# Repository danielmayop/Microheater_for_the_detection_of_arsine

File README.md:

# Microcalentador para la detección de arsina

Microcalentador con control de temperatura para un sensor de arsina. El repositorio reúne el firmware y los scripts, el diseño de la placa, las simulaciones y las mediciones.

| Carpeta | Contenido |
|---|---|
| `Codigos/` | Firmware del controlador y scripts de MATLAB para identificar el modelo |
| `Kicad/` | Esquemático y placa del controlador de temperatura |
| `LTspice/` | Simulaciones |
| `Imagenes/`, `Hoja de datos/`, `paper/` | Fotos, gráficas y documentación |

## Respuesta transitoria del microcalentador (encendido y apagado)

Se midió la temperatura del microcalentador con duty de 30, 40, 50, 60, 70, 80, 90 y 100 %: unos 10 min encendido y luego el enfriamiento, en dos configuraciones:

- **Aire libre:** sensor sobre la parte resistiva.
- **Dentro de la caja:** el microcalentador dentro de una caja, midiendo la temperatura de su interior.

**Parte resistiva, aire libre**

**Dentro de la caja**

### Conclusiones del transitorio

**Encendido.** Las curvas suben a velocidades distintas porque cada duty apunta a una temperatura final distinta: cuanto mayor es el duty, más alta es la temperatura que se busca alcanzar y más rápido sube al principio. Sin embargo, el tiempo que tarda el microcalentador en responder es esencialmente el mismo sin importar el duty: todas las curvas tienen la misma forma y lo único que cambia es su escala. Por eso, al aire libre, el calentamiento se describe bien como un sistema de primer orden con una única constante de tiempo, y el aumento final de temperatura crece de forma proporcional al duty. Dentro de la caja el sensor ve un calentamiento menor y bastante más lento, y la respuesta ya no tiene un solo tiempo característico: hay una parte rápida, parecida a la del calentador al aire libre, y otra mucho más lenta que sigue evolucionando cuando se apaga el calentador, de modo que nunca llega a un régimen estacionario durante la medición.

**Apagado.** Al apagar, lo más caliente se enfría más rápido en valores absolutos, pero eso también le pasa a cualquier sistema lineal, así que por sí solo no demuestra no linealidad. Lo que sí la muestra es comparar las curvas normalizadas: al aire libre, cuanto más caliente está el microcalentador, más rápido se enfría en proporción, algo esperable si las pérdidas de calor hacia el ambiente crecen con la temperatura. Dentro de la caja no se ve esa dependencia, y el enfriamiento tiene una cola lenta: pasados varios minutos desde el apagado la temperatura todavía no volvió a la inicial, por lo que el registro es corto para fijar bien su constante de tiempo de enfriamiento.

### Función de transferencia

Cada curva se ajustó con un modelo de primer orden (`Codigos/Matlab Modelo/construir_tf.m`):

- Encendido: `G_on(s) = K_on / (τ_on·s + 1)`, con `K_on` en °C (el aumento final de temperatura para ese duty) y `τ_on` en s.
- Apagado: `G_off(s) = 1 / (τ_off·s + 1)`, con `τ_off` en s.

**Parte resistiva, aire libre**

| Duty [%] | K_on [°C] | τ_on [s] | τ_off [s] | T_amb [°C] | G_on(s) |
|---:|---:|---:|---:|---:|---|
| 100 | 36,693 | 81,355 | 56,548 | 23,658 | `36,693 / (81,355·s + 1)` |
| 90 | 35,373 | 65,085 | 66,869 | 23,483 | `35,373 / (65,085·s + 1)` |
| 80 | 32,303 | 72,815 | 63,468 | 23,336 | `32,303 / (72,815·s + 1)` |
| 70 | 27,813 | 71,551 | 65,861 | 23,248 | `27,813 / (71,551·s + 1)` |
| 60 | 23,95 | 74,366 | 70,117 | 22,567 | `23,95 / (74,366·s + 1)` |
| 50 | 19,382 | 61,978 | 68,129 | 22,578 | `19,382 / (61,978·s + 1)` |
| 40 | 15,919 | 73,312 | 66,356 | 22,53 | `15,919 / (73,312·s + 1)` |
| 30 | 11,922 | 67,811 | 72,854 | 22,109 | `11,922 / (67,811·s + 1)` |

**Dentro de la caja**

| Duty [%] | K_on [°C] | τ_on [s] | τ_off [s] | T_amb [°C] | G_on(s) |
|---:|---:|---:|---:|---:|---|
| 100 | 26,89 | 116,03 | 130,21 | 24,323 | `26,89 / (116,03·s + 1)` |
| 90 | 23,252 | 115,96 | 125,4 | 24,625 | `23,252 / (115,96·s + 1)` |
| 80 | 20,22 | 120,34 | 148,24 | 24,032 | `20,22 / (120,34·s + 1)` |
| 70 | 18,15 | 119,87 | 125,55 | 24,134 | `18,15 / (119,87·s + 1)` |
| 60 | 15,551 | 138,71 | 131,22 | 23,7 | `15,551 / (138,71·s + 1)` |
| 50 | 12,525 | 117,3 | 154,28 | 23,328 | `12,525 / (117,3·s + 1)` |
| 40 | 9,8572 | 124,09 | 126,49 | 23,1 | `9,8572 / (124,09·s + 1)` |
| 30 | 7,6401 | 116,94 | 140,92 | 22,901 | `7,6401 / (116,94·s + 1)` |

Son los valores que entrega `main_comparacion_duty.m`. En la caja el modelo de primer orden es una aproximación: la curva tiene dos escalas de tiempo, y los `t_on`/`t_off` que usa el script no coinciden con los datos en varias corridas.

## Etapa de amplificación de corriente

El ESP32 genera la señal PWM (en el firmware: GPIO 25, 1 kHz, 8 bits de resolución), pero no puede entregar la corriente que necesita el microcalentador. Por eso la señal pasa por tres etapas en cascada: un **optoacoplador**, un **transistor bipolar (BJT)** y un **MOSFET** que conmuta la corriente del calentador.

La fuente `V1` representa la salida PWM del ESP32 (pulso de 0 a 3 V, período de 1 ms, 0,5 ms en alto, es decir 50 % de duty) y `V2` es la alimentación `Vcc` de 5,5 V.

### Etapas del circuito

1. **Optoacoplador (`U1`, `R1`, `R2`).** La señal del ESP32 enciende el LED del optoacoplador a través de `R1` (330 Ω), que fija la corriente del LED. El fototransistor de salida conduce cuando el LED está encendido y `R2` (4,6 kΩ) a masa mantiene su salida en 0 V cuando el LED está apagado. La función de esta etapa es acoplar la lógica del ESP32 con la etapa de potencia sin conectarlas eléctricamente.
2. **BJT como seguidor por emisor (`Q1`, `R4`, `R5`).** La salida del optoacoplador es una señal débil: puede entregar muy poca corriente. El transistor `Q1` funciona como un "refuerzo" de esa señal, sin cambiarla.
   - **Qué hace.** El optoacoplador maneja solo una corriente muy pequeña (la de la base de `Q1`), y `Q1` entrega por el emisor una corriente mucho mayor, tomada de `Vcc`, para cargar la compuerta del MOSFET.
   - **Qué tensión entrega.** La tensión del emisor copia a la de la base, unos 0,7 V más baja. Por eso se llama "seguidor": la salida sigue a la entrada. Si el optoacoplador pone la base en alto, el emisor queda en alto; si la pone en 0 V, el emisor baja a 0 V.
   - **`R5` (330 Ω).** Está entre el emisor y la compuerta del MOSFET y limita el pico de corriente al cargar la compuerta.
   - **`R4` (10 kΩ).** Va de la compuerta a masa y la descarga cuando `Q1` deja de conducir, porque el seguidor solo puede entregar corriente, no absorberla. Sin `R4`, la compuerta quedaría cargada y el MOSFET no se apagaría.
3. **MOSFET como interruptor (`M1`, `R6`, `R3`).** `M1` (IRFHM830) tiene la fuente a masa y se comporta como un interruptor: con la compuerta alta conduce y con la compuerta en 0 V se corta. La corriente la fijan `Vcc` y las resistencias en serie: `R3` (0,75 Ω) representa al microcalentador y `R6` (4,8 Ω) es la resistencia serie.

### Resultado de la simulación

La traza verde es la tensión sobre `R3` (el calentador) y la azul la corriente que lo atraviesa, durante 10 ms (10 períodos). Son pulsos cuadrados con el mismo período y el mismo ancho que la señal de entrada: la corriente es cero con el PWM en bajo y se mantiene constante, en un valor cercano a 1 A, con el PWM en alto. Es decir, las tres etapas transmiten el PWM sin deformarlo de forma apreciable a esta escala.

### Simulación y placa

La simulación usa componentes distintos de los de la placa (`Kicad/Controlador_temp/`), con la misma topología:

| Función | Simulación (LTspice) | Placa (KiCad) |
|---|---|---|
| Entrada | `V1`, pulso de 0 a 3 V, 1 kHz | PWM del ESP32 (GPIO 25) |
| Optoacoplador | `U1`, 4N25 | `U2`, 4N35 |
| Resistencia del LED | `R1`, 330 Ω | `R3`, 330 Ω |
| Resistencia a masa del fototransistor | `R2`, 4,6 kΩ | `preset2`, trimmer de 5 kΩ |
| BJT | `Q1`, 2N3904 | `Q1`, BD911 |
| Resistencia a masa del emisor | `R4`, 10 kΩ | `R5`, 10 kΩ |
| Resistencia de compuerta | `R5`, 330 Ω | `R6`, 330 Ω |
| MOSFET | `M1`, IRFHM830 | `Q2`, IRLZ44N |
| Resistencia serie | `R6`, 4,8 Ω | `Rs1`, 4,8 Ω |
| Microcalentador | `R3`, 0,75 Ω | conector `Calent1` |
| Alimentación | `V2`, 5,5 V | módulo `PS1` (MC00100) |

## Controlador: on-off frente a PID

Para mantener el microcalentador en la temperatura de consigna (*setpoint*) se compararon dos estrategias de control habituales: el controlador **on-off** (con histéresis) y el controlador **PID**. En este proyecto se eligió el **on-off**.

### Descripción breve

**On-off (todo o nada).** La salida solo tiene dos estados: encendida o apagada. En calefacción se enciende por debajo del setpoint y se apaga por encima, por lo que la temperatura oscila de forma continua alrededor de la consigna. Para evitar conmutaciones muy rápidas se agrega una **histéresis** (una banda alrededor del setpoint): una banda más ancha reduce la frecuencia de conmutación pero aumenta la oscilación y el sobreimpulso. Es el esquema más simple y barato, y se usa donde no se necesita gran precisión ([x-engineer](https://x-engineer.org/?p=3309), [Omega](https://es.omega.com/temperature/Z/controlleroperation.html)).

**PID.** Calcula una salida continua combinando tres acciones sobre el error: la proporcional (reacciona al error actual), la integral (elimina el error permanente acumulándolo) y la derivativa (anticipa la tendencia). Es más preciso y estable que el on-off, pero exige **sintonizar** tres parámetros y es más complejo ([Omega](https://es.omega.com/temperature/Z/controlleroperation.html)). En sistemas térmicos lentos o con retardo, la acción integral puede acumularse mientras la salida está saturada (*integral windup*) y provocar sobreimpulso y oscilaciones, por lo que requiere medidas anti-windup y una sintonización conservadora ([Industrial Monitor Direct](https://industrialmonitordirect.com/blogs/knowledgebase/pid-integral-windup-fix-for-slow-temperature-control-systems)).

### Comparación

| Aspecto | On-off con histéresis | PID |
|---|---|---|
| Salida | Solo encendido o apagado | Continua (duty variable) |
| Precisión en el setpoint | Oscila dentro de una banda | Alta, sin error permanente (con acción integral) |
| Sobreimpulso | Presente, crece con la histéresis | Puede minimizarse si está bien sintonizado |
| Complejidad | Muy baja (una comparación) | Mayor: tres parámetros y anti-windup |
| Sintonización | Solo el ancho de la histéresis | Requiere un modelo o ensayos |
| Conmutación | Frecuente | Salida más suave |
| Recursos | Mínimos | Cálculo periódico con tiempo de muestreo fijo |

### Ventajas y desventajas para este microcalentador

**Ventajas del on-off en esta aplicación**

- **Implementación mínima.** En el firmware (`control.cpp`) el control es una comparación con histéresis de 1 °C: se enciende por debajo de `setpoint - 1 °C`, se apaga al llegar al `setpoint` y mantiene su estado dentro de la banda. No necesita tiempo de muestreo fijo ni parámetros que sintonizar.
- **Sin desgaste por conmutación.** La conmutación se hace con un MOSFET (etapa de amplificación de corriente) y no con un relé mecánico, así que la conmutación frecuente no es un problema de vida útil, que es la principal desventaja habitual del on-off.
- **Dinámica lenta y relativamente simple.** El microcalentador responde como un sistema de primer orden con constante de tiempo de ≈ 1 min al aire libre, por lo que una banda de 1 °C da ciclos de conmutación de varios segundos o más y no a una frecuencia que el MOSFET no pueda seguir.
- **Calentamiento más rápido.** Al encender con el 100 % de duty el sistema sube con la máxima velocidad que permite la etapa de potencia, sin esperar a que un integrador acumule.
- **Seguridad sencilla.** Junto con el límite de 80 °C del firmware y el apagado ante lectura inválida del NTC, el comportamiento es fácil de verificar.

**Desventajas del on-off en esta aplicación**

- **Rizado de temperatura.** La temperatura nunca queda fija: oscila alrededor del setpoint con una amplitud que depende de la histéresis y de la inercia térmica. Si la detección de arsina fuera sensible a pequeñas variaciones de la temperatura del sensor, esto sería la limitación principal.
- **Sobreimpulso por el retardo.** El NTC no está exactamente sobre la resistencia calefactora, y en la caja el sistema tiene dos escalas de tiempo (≈ 1 min y ≈ 5–9 min). Al apagar, la temperatura puede seguir subiendo un poco antes de bajar, y el calor remanente ocasiona que el exceso sobre la consigna dependa de las condiciones de la medición.
- **Potencia máxima en cada ciclo.** Siempre se calienta con la potencia total (≈ 4,7 W disipados en `R6` según la simulación), lo que genera más estrés térmico y un consumo pico mayor que un control que reduce la potencia al acercarse al setpoint.
- **No aprovecha el PWM.** La etapa de potencia ya permite variar el duty (PWM de 1 kHz y 8 bits en el GPIO 25), pero en el esquema on-off solo se usan los valores 0 y 255.

**Qué aportaría un PID**

- Una salida suave: al acercarse a la temperatura deseada reduciría el duty y el rizado sería mucho menor, con error permanente nulo.
- Un mejor desempeño ante perturbaciones como cambios de temperatura ambiente, caja o corrientes de aire, que modifican las pérdidas térmicas.
- Como costo, habría que sintonizarlo y proteger la acción integral contra *windup* durante el calentamiento inicial, donde el actuador está saturado al 100 %.

### Elección para el proyecto

Se eligió el **controlador on-off con histéresis** porque la aplicación no exige regulación de alta precisión, la implementación es muy simple y robusta en el ESP32 y la conmutación del MOSFET no sufre desgaste. A cambio se acepta un rizado de temperatura acotado por la histéresis de 1 °C.

Si más adelante se necesitara menor rizado, los modelos identificados en la sección de la función de transferencia (ganancia estática ≈ 0,40 °C por % de duty y constante de tiempo ≈ 60 s al aire libre) y el PWM ya disponible en el hardware permitirían sintonizar un PID sin modificar la placa.

### Fuentes

- [On-off control system (x-engineer.org)](https://x-engineer.org/?p=3309)
- [Controladores on-off, proporcionales y PID (Omega)](https://es.omega.com/temperature/Z/controlleroperation.html)
- [PID integral windup en sistemas lentos de temperatura (Industrial Monitor Direct)](https://industrialmonitordirect.com/blogs/knowledgebase/pid-integral-windup-fix-for-slow-temperature-control-systems)

## Análisis de la ESP32 DevKit V1

La placa de desarrollo ESP32 DevKit V1 ejecuta el control de temperatura, lee los sensores, maneja la pantalla, genera el PWM de la etapa de potencia y transmite los datos por Bluetooth.

### Tabla de entradas y salidas

Se listan los pines que se usan en la placa (según el esquemático) y en el firmware (`Codigos/Arduino IDE ESP32/control_temperatura ver 2/ControlTemperatura/`). Los pines marcados como "previsto" están conectados a un conector de la placa, pero el firmware actual no los usa.

| GPIO | Nombre en la placa | Función en el proyecto | Tipo | Entrada / salida |
|---|---|---|---|---|
| 2 | `D2` | LED de estado: encendido con el sistema activo, apagado con el sistema apagado o ante una falla (NTC inválido o sobretemperatura) | Digital | Salida |
| 5 | `D5` | Datos del segundo sensor DHT22 (previsto) | Digital | Entrada / salida |
| 12 | `D12` | `SO` del módulo MAX6675 (opcional, previsto) | Digital (SPI) | Entrada |
| 13 | `D13` | `CS` del módulo MAX6675 (opcional, previsto) | Digital (SPI) | Salida |
| 14 | `D14` | `SCK` del módulo MAX6675 (opcional, previsto) | Digital (SPI) | Salida |
| 16 | `RX2` | `SDA` del bus I2C (400 kHz) hacia la pantalla OLED SSD1306 (dirección `0x3C`) | Digital (I2C) | Entrada / salida |
| 17 | `TX2` | `SCL` del bus I2C hacia la pantalla OLED | Digital (I2C) | Salida |
| 18 | `D18` | Datos del sensor DHT22 (temperatura ambiente y humedad, cada 2 s) | Digital | Entrada / salida |
| 25 | `D25` | Señal PWM (1 kHz, 8 bits) hacia el optoacoplador de la etapa de potencia; con el control on-off toma solo los valores 0 y 255 | PWM | Salida |
| 26 | `D26` | Interruptor de encendido del sistema (pull-up interno; ON = conectado a GND) | Digital | Entrada |
| 34 | `D34` | Potenciómetro que fija el setpoint (ADC de 12 bits) | Analógico (ADC1) | Entrada |
| 35 | `D35` | Divisor del termistor NTC de 10 kΩ, temperatura real usada por el control (ADC de 12 bits, 0 a 3,3 V) | Analógico (ADC1) | Entrada |
| — | `3V3` | Alimentación de 3,3 V para el potenciómetro, el divisor del termistor, los pull-up, la pantalla, el MAX6675 y los DHT22 | Alimentación | Salida |
| — | `GND` | Masa común de la placa | Alimentación | — |
| — | `VIN` | Entrada de 5,5 V desde el módulo reductor (`Vcc`) a través del diodo `D1` | Alimentación | Entrada |

El monitor serie usa el UART0 (`TX0` y `RX0`, GPIO 1 y 3) a través del puerto USB, y el Bluetooth (BLE) es interno del módulo, por lo que no ocupan pines de la placa.

## Diseño PCB

La placa se diseñó en KiCad (`Kicad/Controlador_temp/`). El esquemático reúne en una sola placa la alimentación, la ESP32 DevKit V1, la etapa de potencia del microcalentador y los conectores de los sensores y de la pantalla.

### Etapas de la placa

- **Alimentación.** La placa se alimenta con 19 V a través de un conector *jack* (`J1`). El pulsador `Btn2` está en serie con la entrada y enciende y apaga la alimentación de toda la placa. Un módulo reductor DC-DC (`PS1`, MC00100) baja los 19 V a 5,5 V (red `Vcc`), con un capacitor de 1000 µF (`C2`) en la salida. Esa tensión alimenta la etapa de potencia y, a través de un diodo Schottky (`D1`), el pin `VIN` de la ESP32, que genera los 3,3 V (`3V3`) para los sensores y la pantalla.
- **Microcontrolador.** La ESP32 DevKit V1 (`U1`) ejecuta el control de temperatura. El pulsador `Btn1` (con `R1` de 330 Ω) está conectado al GPIO 26 (`boton1`) y enciende y apaga el sistema de control. Los pines que usa el firmware están en la sección anterior.
- **Etapa de amplificación de corriente.** Es la que se describió en la sección anterior: el PWM del GPIO 25 pasa por el optoacoplador 4N35 (`U2`), un BJT BD911 (`Q1`) y un MOSFET IRLZ44N (`Q2`), que conmuta la corriente del microcalentador conectado al terminal `Calent1` en serie con `Rs1` de 4,8 Ω.
- **Consigna de temperatura.** El potenciómetro `RV1`, alimentado con 3,3 V, entrega al GPIO 34 (`potenc`) la tensión que fija la temperatura a la que se quiere llevar el microcalentador.
- **Medición de temperatura.** El conector `J4` recibe el termistor, que junto con la resistencia `R2` de 100 kΩ forma un divisor de tensión cuya salida va al GPIO 35 (`D35`).
- **Pantalla.** El conector `J2` lleva `GND`, `3V3` y las líneas `SDA` y `SCL` del bus I2C hacia la pantalla LCD/OLED.
- **Termocupla (opcional).** El conector `J3` está previsto para un módulo MAX6675, conectado por SPI (`SCK`, `SO`, `CS`) a los GPIO 14, 12 y 13. Es opcional y el firmware actual no lo usa.
- **Sensores de temperatura y humedad.** Los conectores `J5` y el de `SENS-1` permiten conectar dos sensores DHT (en el esquemático figuran como DHT22; el DHT21 usa el mismo protocolo de un solo hilo), con resistencias de pull-up de 10 kΩ a 3,3 V (`R4` y `R7`) sobre las líneas `DHT22_1` (GPIO 18) y `DHT22_2` (GPIO 5). El firmware actual solo lee el primero.

### Lista de componentes

| Referencia | Componente | Valor / modelo | Cant. |
|---|---|---|---|
| `U1` | Placa de desarrollo | ESP32 DevKit V1 | 1 |
| `PS1` | Módulo reductor DC-DC | MC00100 (LM2596) | 1 |
| `U2` | Optoacoplador | 4N35 | 1 |
| `Q1` | Transistor BJT | BD911 | 1 |
| `Q2` | MOSFET canal N | IRLZ44N | 1 |
| `D1` | Diodo | Tipo Schottky (DO-41) | 1 |
| `C2` | Capacitor electrolítico | 1000 µF | 1 |
| `R1`, `R3`, `R6` | Resistencia | 330 Ω | 3 |
| `R4`, `R5`, `R7` | Resistencia | 10 kΩ | 3 |
| `R2` | Resistencia | 100 kΩ | 1 |
| `Rs1` | Resistencia de potencia | 4,8 Ω | 1 |
| `preset2` | Trimmer | 5 kΩ | 1 |
| `RV1` | Potenciómetro | Lineal | 1 |
| `J1` | Conector jack DC | 19 V | 1 |
| `Btn1`, `Btn2`, `Calent1` | Bornera de 2 pines | 5,08 mm | 3 |
| `J4` | Conector del termistor | 2 pines | 1 |
| `J2`, `J3`, `J5` | Conector JST XH | 5 pines | 3 |
| `SENS-1` | Sensor de temperatura y humedad | DHT22 | 1 |
| `H1` a `H4` | Perforación de montaje | M3 | 4 |

### Diseño y placa real

Arriba se ve el diseño 3D generado en KiCad y abajo la placa fabricada, por la cara superior (izquierda) y la cara inferior (derecha). Las fotos de la placa real están giradas 90° para compararlas con el diseño.

La placa real respeta el diseño: mantiene la distribución de las etapas, las pistas de las dos caras, las perforaciones de montaje y la serigrafía (nombres de conectores, referencias de componentes y la inscripción "PROYECTO 2026"). El módulo reductor figura serigrafiado como `STEP DOWN LM2596` y el módulo de la ESP32 tiene el recorte para su antena. Las fotos corresponden a la placa sin componentes soldados, con todas las perforaciones y pads listos para el montaje.

## Conexión a la página

Los datos que envía la ESP32 se visualizan en una página web, **GIAQA Monitoreo Bluetooth**, diseñada en Lovable. La ESP32 transmite por Bluetooth de baja energía (BLE) y la página se conecta directamente desde el navegador mediante Web Bluetooth.

**Enlace a la página:** [https://id-preview--22e80b2b-a717-4908-83b7-207b0a4aaa5b.lovable.app](https://id-preview--22e80b2b-a717-4908-83b7-207b0a4aaa5b.lovable.app)

**Proyecto en Lovable:** [BLE Dashboard](https://lovable.dev/projects/22e80b2b-a717-4908-83b7-207b0a4aaa5b)

### Qué hace la página

- **Mediciones.** Permite conectar la ESP32 por Bluetooth, recibir las variables en tiempo real (temperatura real, temperatura y humedad del DHT22, setpoint, estado del calentador y tiempo) y graficarlas en vivo. Incluye un registro de eventos de la conexión, el inicio y la pausa de la adquisición, y un modo de simulación para probar la página sin la placa.
- **Procesamiento.** Ofrece herramientas para procesar y analizar los datos adquiridos.
- **Historial y exportación.** Se pueden guardar las mediciones, revisarlas, graficarlas, renombrarlas, eliminarlas y exportarlas en formato CSV o TXT.
- **Cuentas y mediciones compartidas.** Hay perfiles de usuario opcionales y se pueden compartir mediciones en vivo, en modo solo lectura, mediante códigos de acceso.
- **Teoría y guías.** Tiene secciones de contenido teórico y guías de uso.

### Cómo se comunica con la ESP32

La ESP32 se publica como servidor BLE con el servicio *Nordic UART* (NUS). Envía los datos por notificaciones en la característica de transmisión, en mensajes con formato JSON (por ejemplo, `temperatura_real`, `setpoint`, `calentador`), y la página puede enviarle comandos por la característica de recepción. La conexión requiere un navegador con Web Bluetooth, como Chrome o Edge en escritorio o en Android.

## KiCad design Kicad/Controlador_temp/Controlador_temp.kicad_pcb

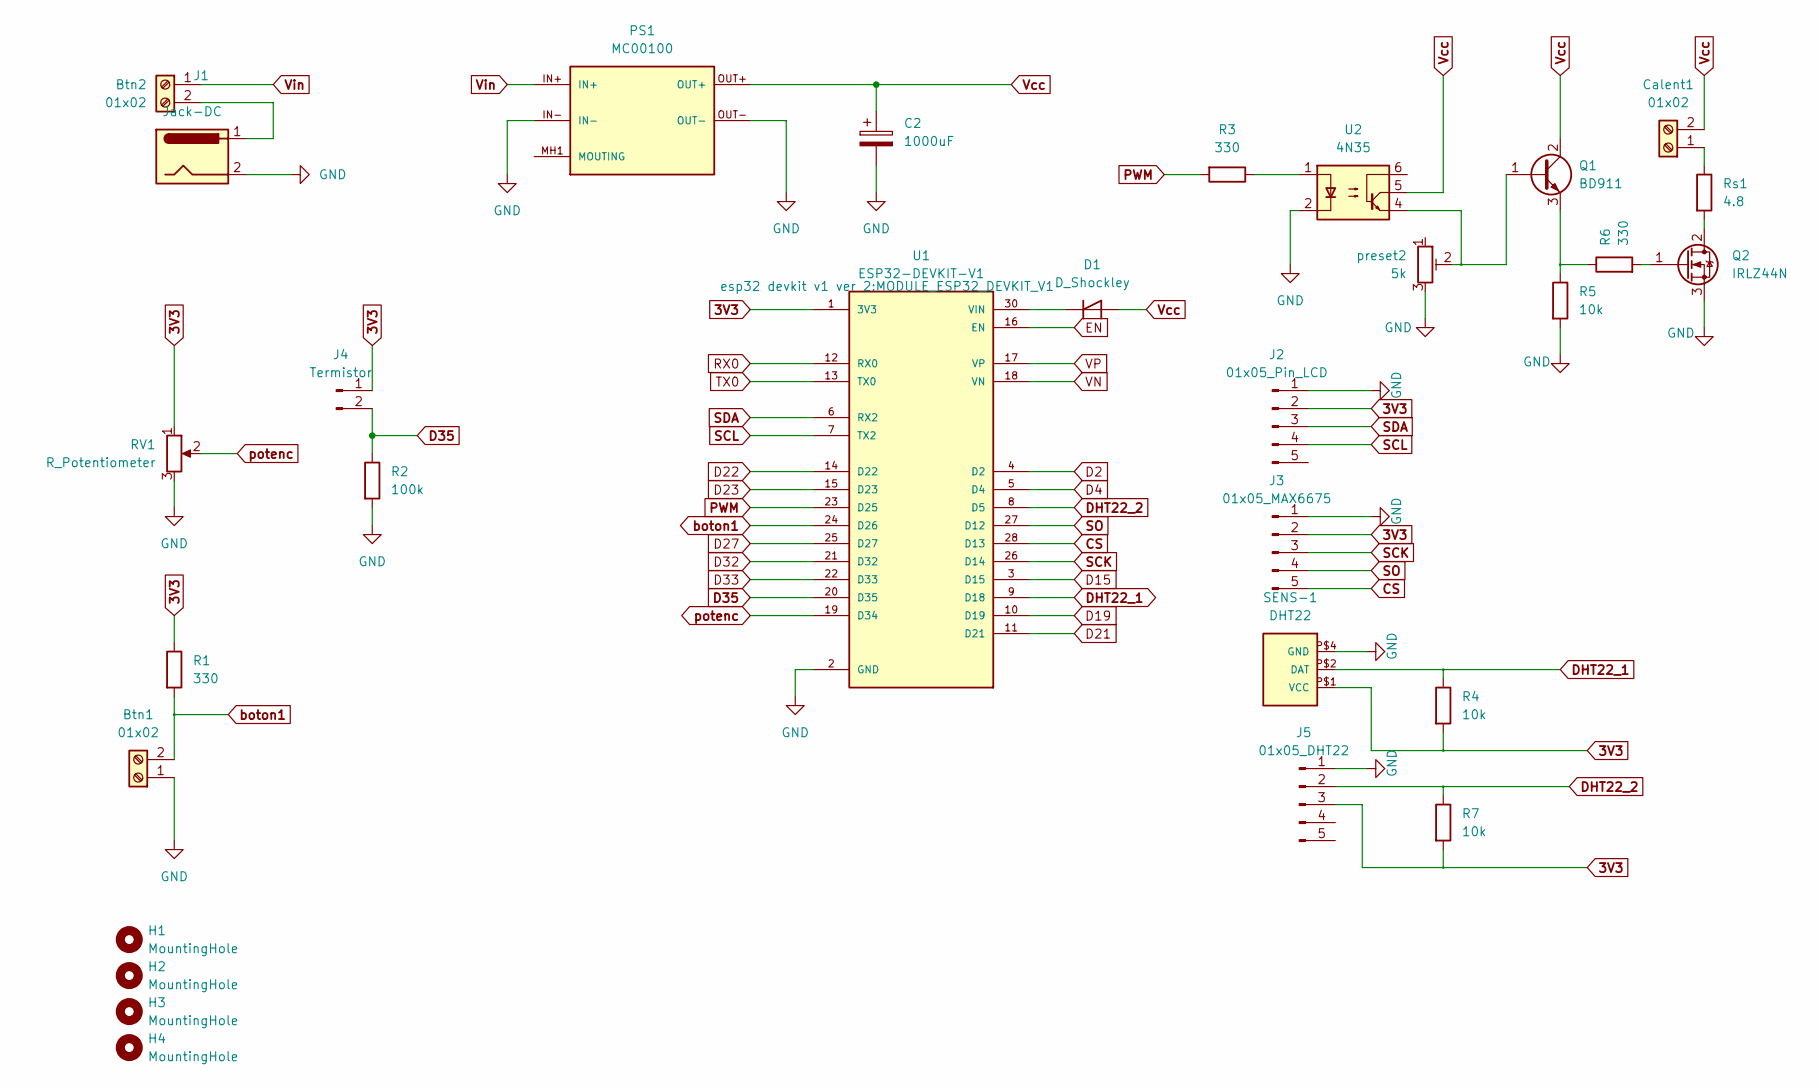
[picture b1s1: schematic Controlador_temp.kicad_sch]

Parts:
Btn1, Btn2: 01x02; TerminalBlock_Phoenix_MKDS-1,5-2-5.08_1x02_P5.08mm_Horizont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
C2: 1000uF; CP_Radial_D12.5mm_P5.00mm
Calent1: 01x02; TerminalBlock_Phoenix_MKDS-1,5-2-5.08_1x02_P5.08mm_Horizont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
D1: D_Shockley; D_DO-41_SOD81_P10.16mm_Horizontal
H1, H2, H3, H4: MountingHole; MountingHole_3.2mm_M3
J1: Jack-DC; BarrelJack_Horizontal
J2: 01x05_Pin_LCD; JST_XH_B5B-XH-A_1x05_P2.50mm_Vertical
J3: 01x05_MAX6675; JST_XH_B5B-XH-A_1x05_P2.50mm_Vertical
J4: Termistor; PinHeader_1x02_P2.54mm_Vertical
J5: 01x05_DHT22; JST_XH_B5B-XH-A_1x05_P2.50mm_Vertical
PS1: MC00100; CONV_MC00100; PARTREV NA
Q1: BD911; TO-220-3_Vertical
Q2: IRLZ44N; TO-220-3_Vertical
R1, R3, R6: 330; R_Axial_DIN0207_L6.3mm_D2.5mm_P10.16mm_Horizontal
R2: 100k; R_Axial_DIN0207_L6.3mm_D2.5mm_P10.16mm_Horizontal
R4, R5, R7: 10k; R_Axial_DIN0207_L6.3mm_D2.5mm_P10.16mm_Horizontal
RV1: R_Potentiometer; Potentiometer_Alps_RK163_Single_Horizontal
Rs1: 4.8; R_Axial_Power_L50.0mm_W9.0mm_P55.88mm
SENS-1: DHT22; SENSOR-DHT11
U1: ESP32-DEVKIT-V1; MODULE_ESP32_DEVKIT_V1; PARTREV N/A
U2: 4N35; DIP-6_W7.62mm
preset2: 5k; Potentiometer_Bourns_3296W_Vertical

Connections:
3V3: J2.2, J3.2, J4.1, J5.3, R1.1, R4.2, R7.2, RV1.1, SENS-1.P$1 (VCC), U1.1 (3V3)
CS: J3.5, U1.28 (D13)
D2: U1.4 (D2)
D4: U1.5 (D4)
D15: U1.3 (D15)
D19: U1.10 (D19)
D21: U1.11 (D21)
D22: U1.14 (D22)
D23: U1.15 (D23)
D27: U1.25 (D27)
D32: U1.21 (D32)
D33: U1.22 (D33)
D35: J4.2, R2.1, U1.20 (D35)
DHT22_1: R4.1, SENS-1.P$2 (DAT), U1.9 (D18)
DHT22_2: J5.2, R7.1, U1.8 (D5)
EN: U1.16 (EN)
GND: Btn1.1, C2.2, J1.2, J2.1, J3.1, J5.1, PS1.IN-, PS1.OUT-, Q2.3 (S), R2.2, R5.2, RV1.3, SENS-1.P$4 (GND), U1.2 (GND), U1.29 (GND), U2.2, preset2.3
unnamed: Btn2.2, J1.1
unnamed: Calent1.1, Rs1.1
unnamed: D1.1 (K), U1.30 (VIN)
unnamed: Q1.1 (B), U2.4, preset2.2
unnamed: Q1.3 (E), R5.1, R6.1
unnamed: Q2.2 (D), Rs1.2
unnamed: Q2.1 (G), R6.2
unnamed: R3.1, U2.1
PWM: R3.2, U1.23 (D25)
RX0: U1.12 (RX0)
SCK: J3.3, U1.26 (D14)
SCL: J2.4, U1.7 (TX2)
SDA: J2.3, U1.6 (RX2)
SO: J3.4, U1.27 (D12)
TX0: U1.13 (TX0)
VN: U1.18 (VN)
VP: U1.17 (VP)
Vcc: C2.1, Calent1.2, D1.2 (A), PS1.OUT+, Q1.2 (C), U2.5
Vin: Btn2.1, PS1.IN+
boton1: Btn1.2, R1.2, U1.24 (D26)
potenc: RV1.2, U1.19 (D34)

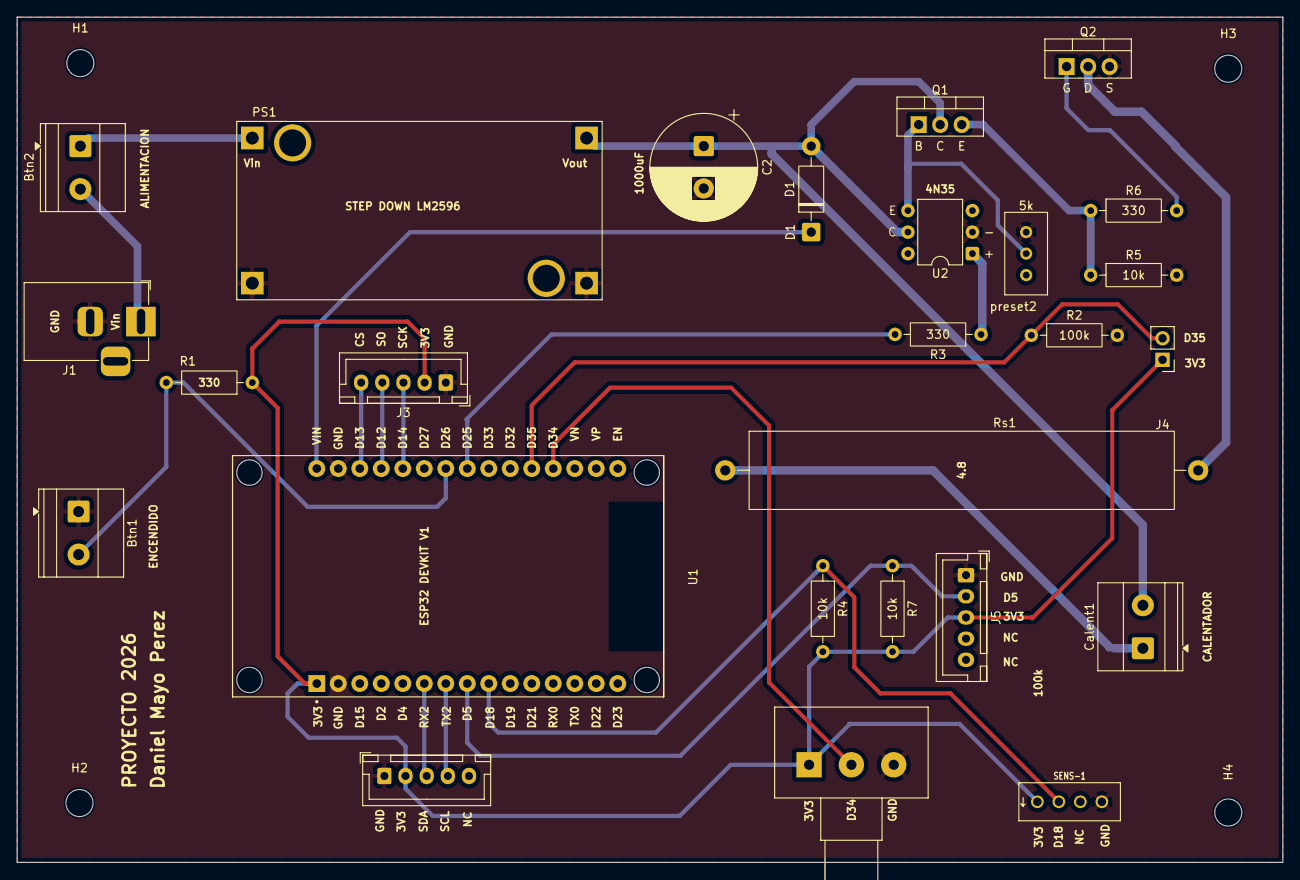
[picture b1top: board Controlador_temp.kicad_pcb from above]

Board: 2 copper layers, 149.6 x 99.9 mm, 30 parts (0 on the bottom side), 23 nets.
